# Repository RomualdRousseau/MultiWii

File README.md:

# MultiWii
Implementation of a MultiWii quadcopter

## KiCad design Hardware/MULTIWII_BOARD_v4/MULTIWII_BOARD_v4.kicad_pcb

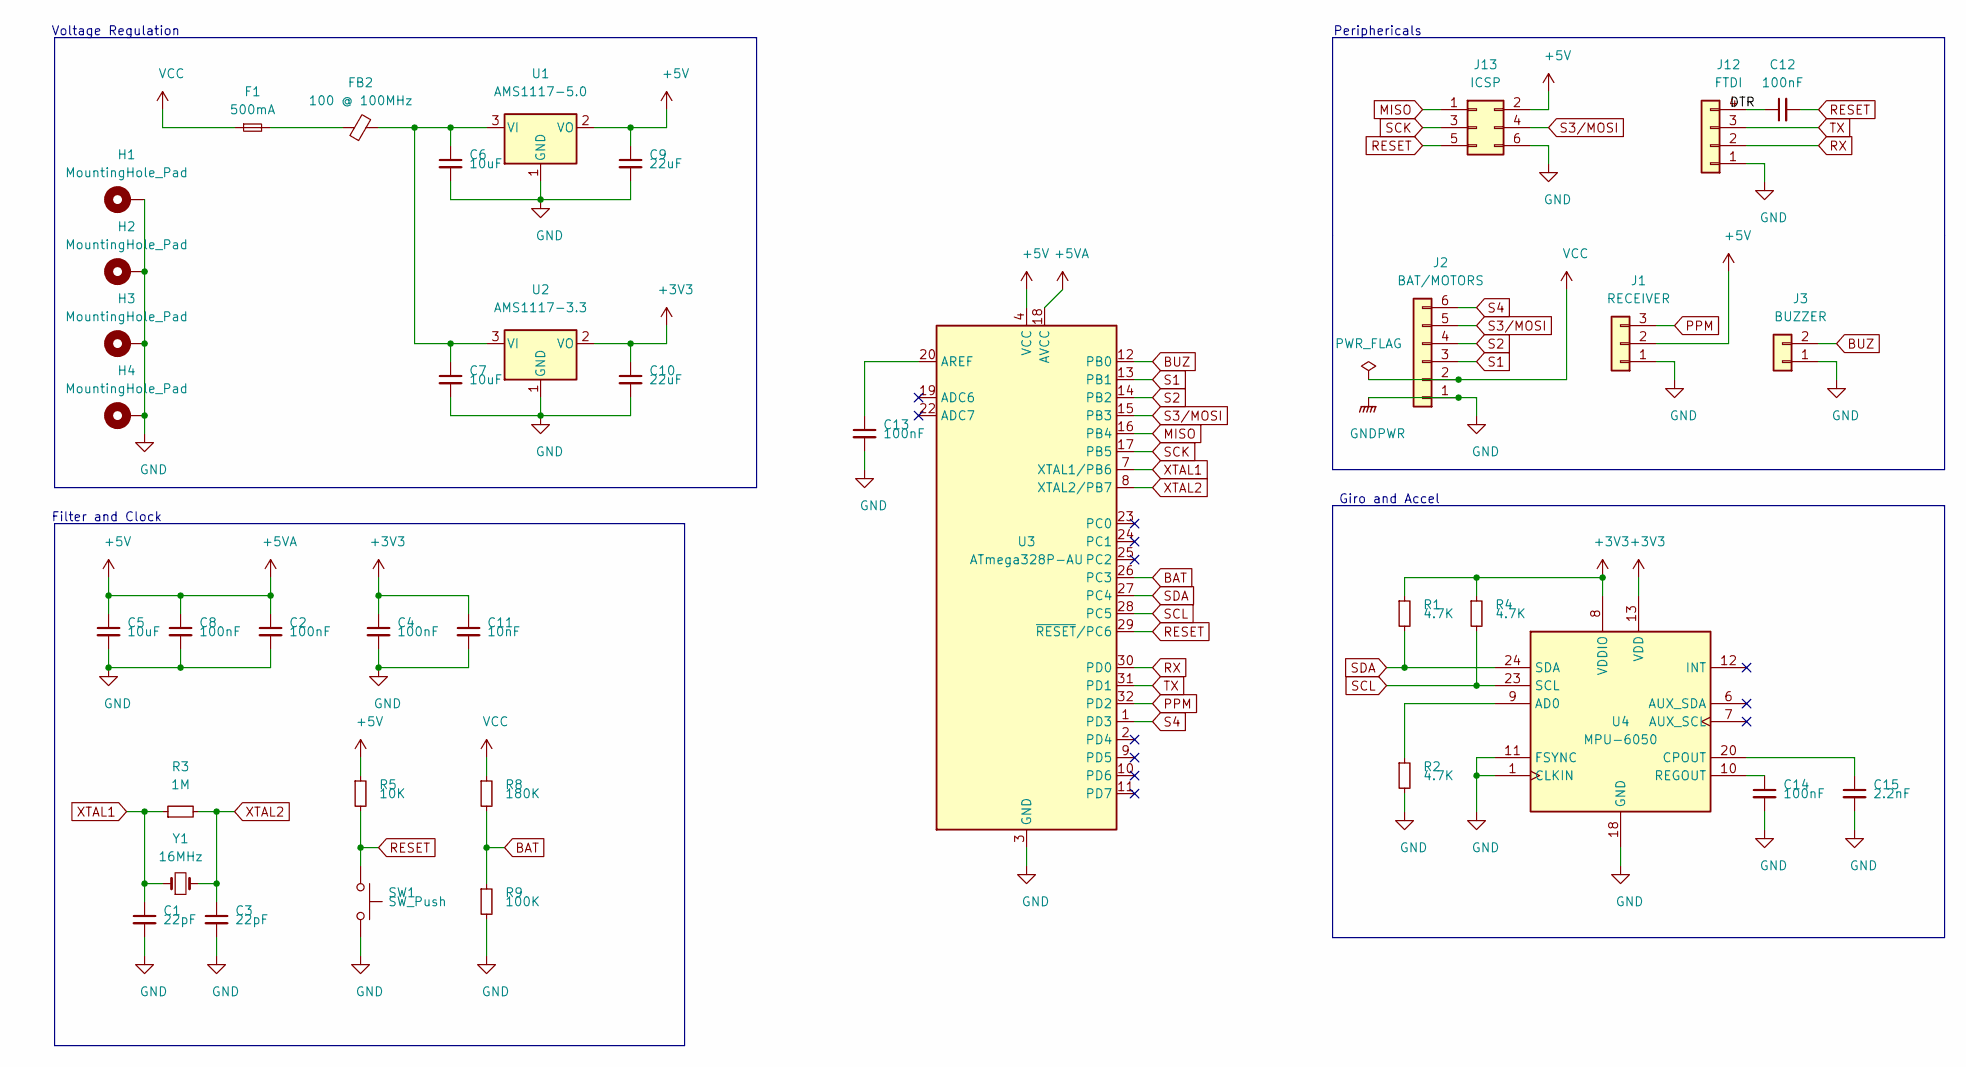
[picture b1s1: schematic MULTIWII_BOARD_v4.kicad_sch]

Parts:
C1, C3: 22pF; C_0603_1608Metric
C2, C4, C8, C12, C13, C14: 100nF; C_0603_1608Metric
C5: 10uF; C_0603_1608Metric
C6, C7: 10uF; C_0805_2012Metric
C9, C10: 22uF; C_0805_2012Metric
C11: 10nF; C_0603_1608Metric
C15: 2.2nF; C_0603_1608Metric
F1: 500mA; Fuse_0603_1608Metric
FB2: 100 @ 100MHz; L_0805_2012Metric
H1, H2, H3, H4: MountingHole_Pad; MountingHole_3.2mm_M3
J1: RECEIVER; Molex_PicoBlade_53261-0371_1x03-1MP_P1.25mm_Horizontal
J2: BAT/MOTORS; Molex_PicoBlade_53261-0671_1x06-1MP_P1.25mm_Horizontal
J3: BUZZER; PinHeader_1x02_P1.00mm_Vertical_SMD_Pin1Right
J12: FTDI; Molex_PicoBlade_53261-0471_1x04-1MP_P1.25mm_Horizontal
J13: ICSP; PinHeader_1x06_P1.00mm_Vertical_SMD_Pin1Right
R1, R2, R4: 4.7K; R_0603_1608Metric
R3: 1M; R_0603_1608Metric
R5: 10K; R_0603_1608Metric
R8: 180K; R_0603_1608Metric
R9: 100K; R_0603_1608Metric
SW1: SW_Push; SW_Push_1P1T_NO_CK_KMR2
U1: AMS1117-5.0; SOT-223-3_TabPin2
U2: AMS1117-3.3; SOT-223-3_TabPin2
U3: ATmega328P-AU; TQFP-32_7x7mm_P0.8mm
U4: MPU-6050; InvenSense_QFN-24_4x4mm_P0.5mm
Y1: 16MHz; Crystal_SMD_5032-2Pin_5.0x3.2mm

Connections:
+3V3: C4.1, C10.1, C11.1, R1.1, R4.1, U2.2 (VO), U4.8 (VDDIO), U4.13 (VDD)
+5V: C2.1, C5.1, C8.1, C9.1, J1.2, J13.2, R5.1, U1.2 (VO), U3.4 (VCC), U3.6 (VCC), U3.18 (AVCC)
/DTR: C12.1, J12.4
BAT: R8.2, R9.1, U3.26 (PC3)
BUZ: J3.2, U3.12 (PB0)
GND: C1.2, C2.2, C3.2, C4.2, C5.2, C6.2, C7.2, C8.2, C9.2, C10.2, C11.2, C13.2, C14.2, C15.2, H1.1, H2.1, H3.1, H4.1, J1.1, J2.1, J3.1, J12.1, J13.6, R2.2, R9.2, SW1.2, U1.1 (GND), U2.1 (GND), U3.3 (GND), U3.5 (GND), U3.21 (GND), U4.1 (CLKIN), U4.11 (FSYNC), U4.18 (GND)
MISO: J13.1, U3.16 (PB4)
unnamed: C6.1, C7.1, FB2.2, U1.3 (VI), U2.3 (VI)
unnamed: C13.1, U3.20 (AREF)
unnamed: C14.1, U4.10 (REGOUT)
unnamed: C15.1, U4.20 (CPOUT)
unnamed: F1.2, FB2.1
unnamed: R2.1, U4.9 (AD0)
PPM: J1.3, U3.32 (PD2)
RESET: C12.2, J13.5, R5.2, SW1.1, U3.29 (~RESET~/PC6)
RX: J12.2, U3.30 (PD0)
S1: J2.3, U3.13 (PB1)
S2: J2.4, U3.14 (PB2)
S3/MOSI: J2.5, J13.4, U3.15 (PB3)
S4: J2.6, U3.1 (PD3)
SCK: J13.3, U3.17 (PB5)
SCL: R4.2, U3.28 (PC5), U4.23 (SCL)
SDA: R1.2, U3.27 (PC4), U4.24 (SDA)
TX: J12.3, U3.31 (PD1)
VCC: F1.1, J2.2, R8.1
XTAL1: C1.1, R3.1, U3.7 (XTAL1/PB6), Y1.1
XTAL2: C3.1, R3.2, U3.8 (XTAL2/PB7), Y1.2

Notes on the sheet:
Filter and Clock
Voltage Regulation
Periphericals
Giro and Accel

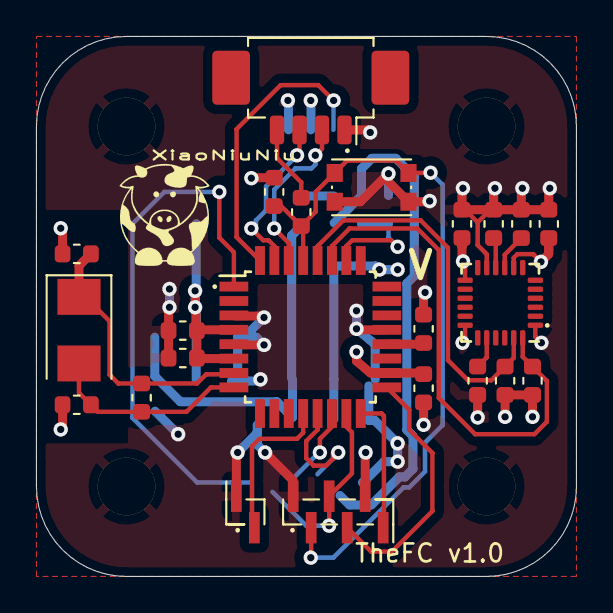
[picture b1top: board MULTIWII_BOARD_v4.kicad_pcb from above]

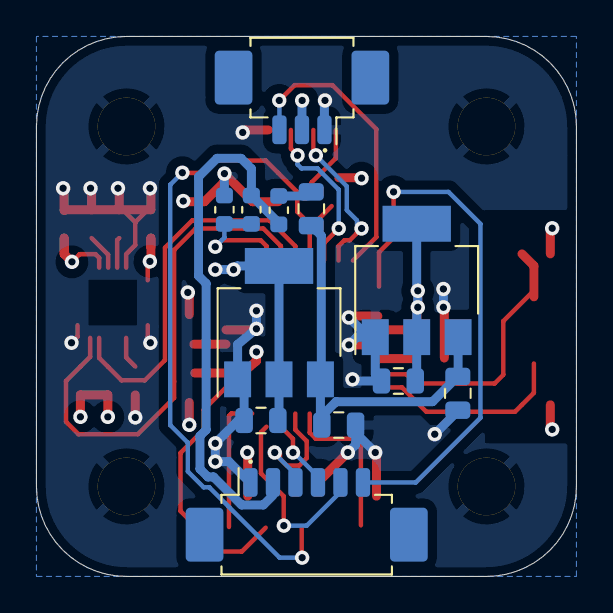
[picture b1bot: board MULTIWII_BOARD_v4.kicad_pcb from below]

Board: 4 copper layers, 30.0 x 30.0 mm, 39 parts (12 on the bottom side), 27 nets.

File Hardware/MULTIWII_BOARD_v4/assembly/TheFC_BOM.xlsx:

Ref | Qnty | Value | Footprint | MFRPart
C1, C3 | 2 | 22pF | Capacitor_SMD:C_0603_1608Metric | CL10C220JB8NNNC
C2, C4, C8, C12, C13, C14 | 6 | 100nF | Capacitor_SMD:C_0603_1608Metric | CC0603KRX7R9BB104
C5 | 1 | 10uF | Capacitor_SMD:C_0603_1608Metric | CL10A106KP8NNNC
C6, C7 | 2 | 10uF | Capacitor_SMD:C_0805_2012Metric | CL21A106KAYNNNE
C9, C10 | 2 | 22uF | Capacitor_SMD:C_0805_2012Metric | CL21A226MAQNNNE
C11 | 1 | 10nF | Capacitor_SMD:C_0603_1608Metric | 0603B103K500NT
C15 | 1 | 2.2nF | Capacitor_SMD:C_0603_1608Metric | 0603B222K500NT
F1 | 1 | 500mA | Fuse:Fuse_0603_1608Metric | TLC-FSMD050
FB2 | 1 | 100 @ 100MHz | Inductor_SMD:L_0805_2012Metric | GZ2012D101TF
J1 | 1 | RECEIVER | Connector_Molex:Molex_PicoBlade_53261-0371_1x03-1MP_P1.25mm_Horizontal | 532610371 | 510210300
J2 | 1 | BAT/MOTORS | Connector_Molex:Molex_PicoBlade_53261-0671_1x06-1MP_P1.25mm_Horizontal | 532610671
J12 | 1 | FTDI | Connector_Molex:Molex_PicoBlade_53261-0471_1x04-1MP_P1.25mm_Horizontal | 532610471 | 510210400
R1, R2, R4 | 3 | 4.7K | Resistor_SMD:R_0603_1608Metric | 0603WAF4701T5E
R3 | 1 | 1M | Resistor_SMD:R_0603_1608Metric | 0603WAF1004T5E
R5 | 1 | 10K | Resistor_SMD:R_0603_1608Metric | 0603WAF1002T5E
R8 | 1 | 180K | Resistor_SMD:R_0603_1608Metric | 0603WAF1803T5E
R9 | 1 | 100K | Resistor_SMD:R_0603_1608Metric | 0603WAF1003T5E
SW1 | 1 | SW_Push | Button_Switch_SMD:SW_Push_1P1T_NO_CK_KMR2 | KMR221NGLFS
U1 | 1 | AMS1117-5.0 | Package_TO_SOT_SMD:SOT-223-3_TabPin2 | AMS1117-5.0
U2 | 1 | AMS1117-3.3 | Package_TO_SOT_SMD:SOT-223-3_TabPin2 | AMS1117-3.3
U3 | 1 | ATmega328P-AU | Package_QFP:TQFP-32_7x7mm_P0.8mm | ATMEGA328P-AU
U4 | 1 | MPU-6050 | Sensor_Motion:InvenSense_QFN-24_4x4mm_P0.5mm | MPU-6050
Y1 | 1 | 16MHz | Crystal:Crystal_SMD_5032-2Pin_5.0x3.2mm | X503216MSB2GI

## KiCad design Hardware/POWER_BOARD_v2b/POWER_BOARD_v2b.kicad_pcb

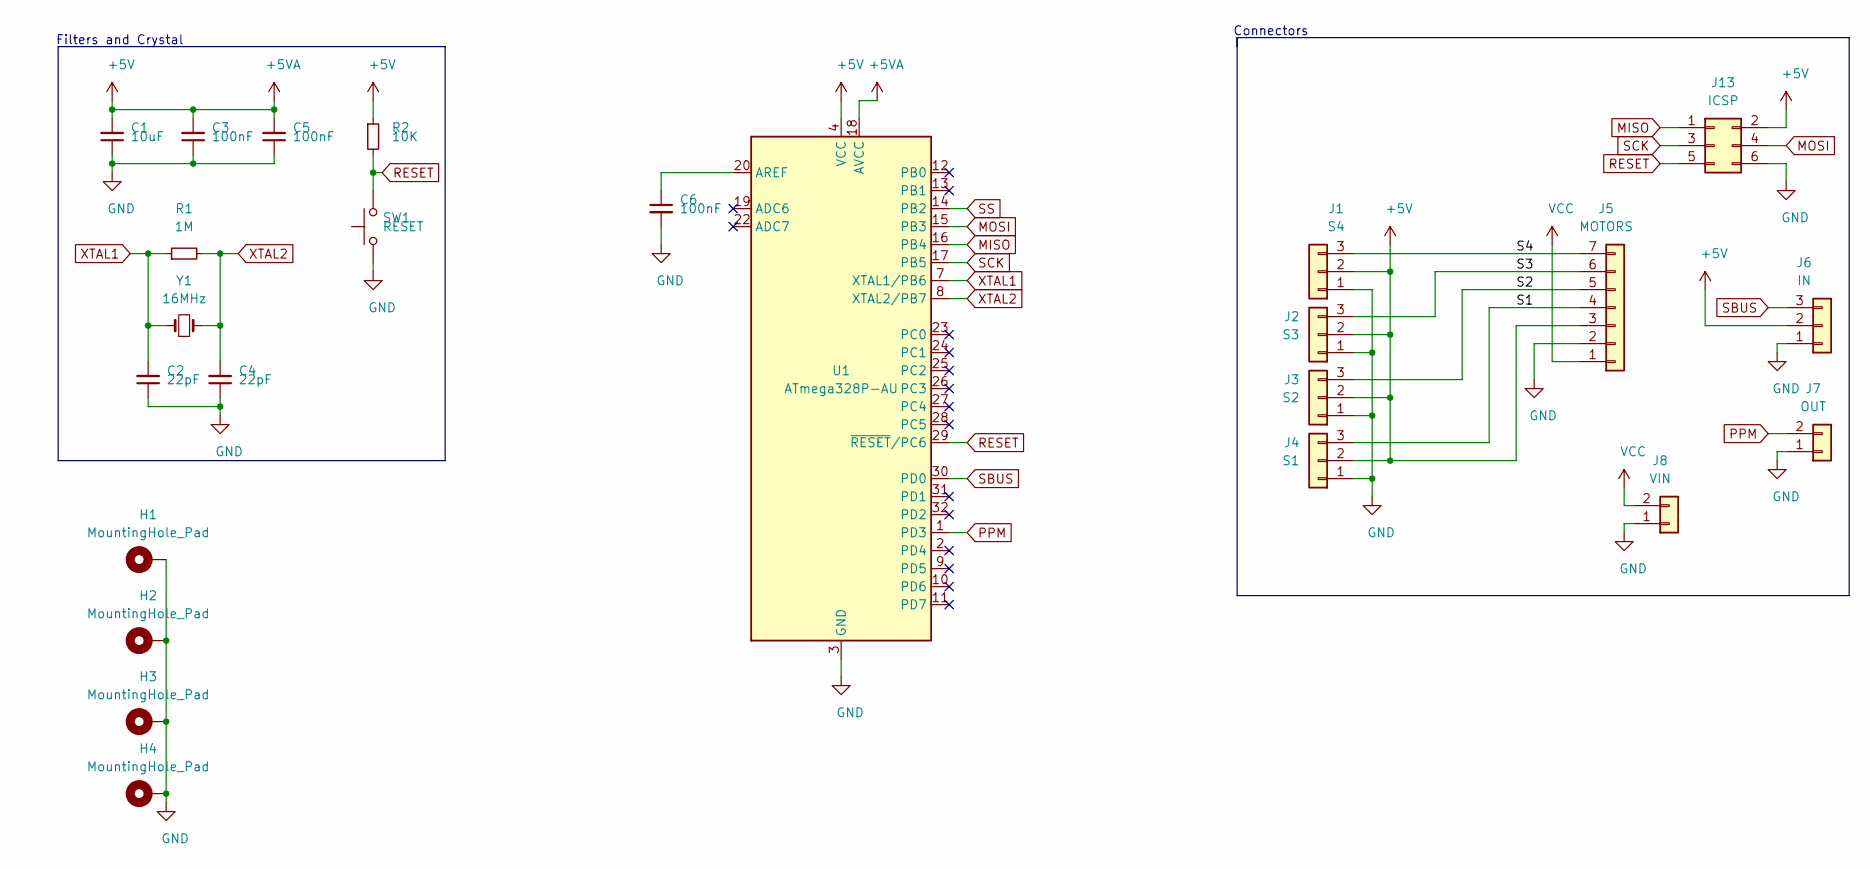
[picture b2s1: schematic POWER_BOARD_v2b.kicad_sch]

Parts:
C1: 10uF; C_0805_2012Metric
C2, C4: 22pF; C_0603_1608Metric
C3, C5, C6: 100nF; C_0603_1608Metric
H1, H2, H3, H4: MountingHole_Pad; MountingHole_3.2mm_M3
J1: S4; PinHeader_1x03_P2.54mm_Vertical
J2: S3; PinHeader_1x03_P2.54mm_Vertical
J3: S2; PinHeader_1x03_P2.54mm_Vertical
J4: S1; PinHeader_1x03_P2.54mm_Vertical
J5: MOTORS; PinHeader_1x07_P2.54mm_Vertical
J6: IN; PinHeader_1x03_P2.54mm_Vertical
J7: OUT; PinHeader_1x02_P2.54mm_Vertical
J8: VIN; PinHeader_1x02_P2.54mm_Vertical
J13: ICSP; PinHeader_2x03_P1.00mm_Vertical_SMD
R1: 1M; R_0603_1608Metric
R2: 10K; R_0603_1608Metric
SW1: RESET; SW_SPST_PTS645
U1: ATmega328P-AU; TQFP-32_7x7mm_P0.8mm
Y1: 16MHz; Crystal_SMD_HC49-SD

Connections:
+5V: C1.2, C3.2, C5.2, J1.2, J2.2, J3.2, J4.2, J5.3, J6.2, J13.2, R2.1, U1.4 (VCC), U1.6 (VCC), U1.18 (AVCC)
/S1: J4.3, J5.4
/S2: J3.3, J5.5
/S3: J2.3, J5.6
/S4: J1.3, J5.7
GND: C1.1, C2.1, C3.1, C4.1, C5.1, C6.2, H1.1, H2.1, H3.1, H4.1, J1.1, J2.1, J3.1, J4.1, J5.2, J6.1, J7.1, J8.1, J13.6, SW1.1, U1.3 (GND), U1.5 (GND), U1.21 (GND)
MISO: J13.1, U1.16 (PB4)
MOSI: J13.4, U1.15 (PB3)
unnamed: C6.1, U1.20 (AREF)
PPM: J7.2, U1.1 (PD3)
RESET: J13.5, R2.2, SW1.2, U1.29 (~RESET~/PC6)
SBUS: J6.3, U1.30 (PD0)
SCK: J13.3, U1.17 (PB5)
SS: U1.14 (PB2)
VCC: J5.1, J8.2
XTAL1: C2.2, R1.1, U1.7 (XTAL1/PB6), Y1.1
XTAL2: C4.2, R1.2, U1.8 (XTAL2/PB7), Y1.2

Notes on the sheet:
Filters and Crystal
Connectors

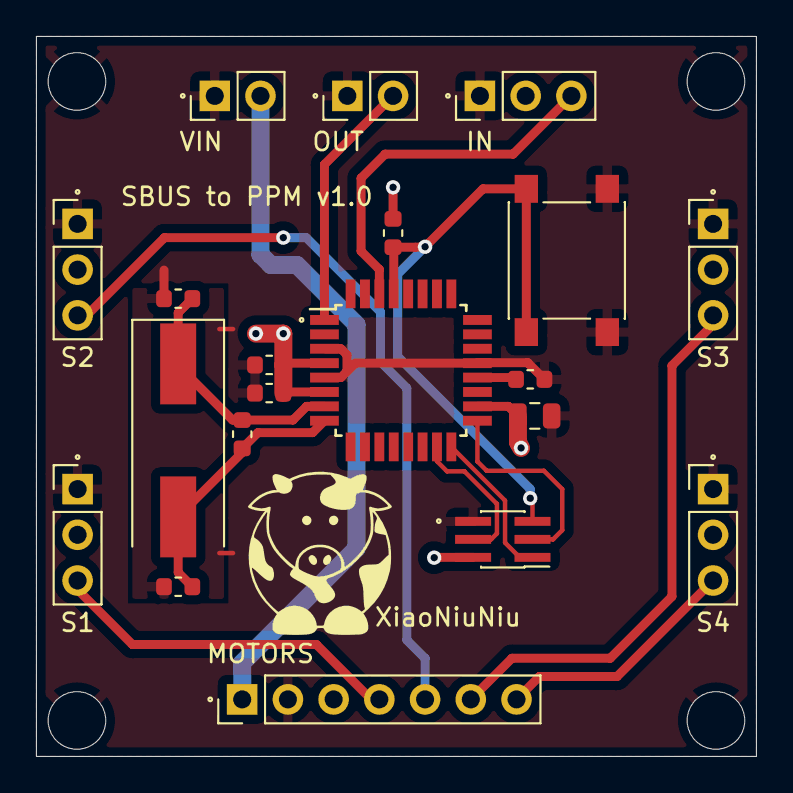
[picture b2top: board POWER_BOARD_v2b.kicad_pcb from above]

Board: 2 copper layers, 40.0 x 40.0 mm, 24 parts (0 on the bottom side), 16 nets.

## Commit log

2021-12-20 Fist version
2021-12-20 First version
